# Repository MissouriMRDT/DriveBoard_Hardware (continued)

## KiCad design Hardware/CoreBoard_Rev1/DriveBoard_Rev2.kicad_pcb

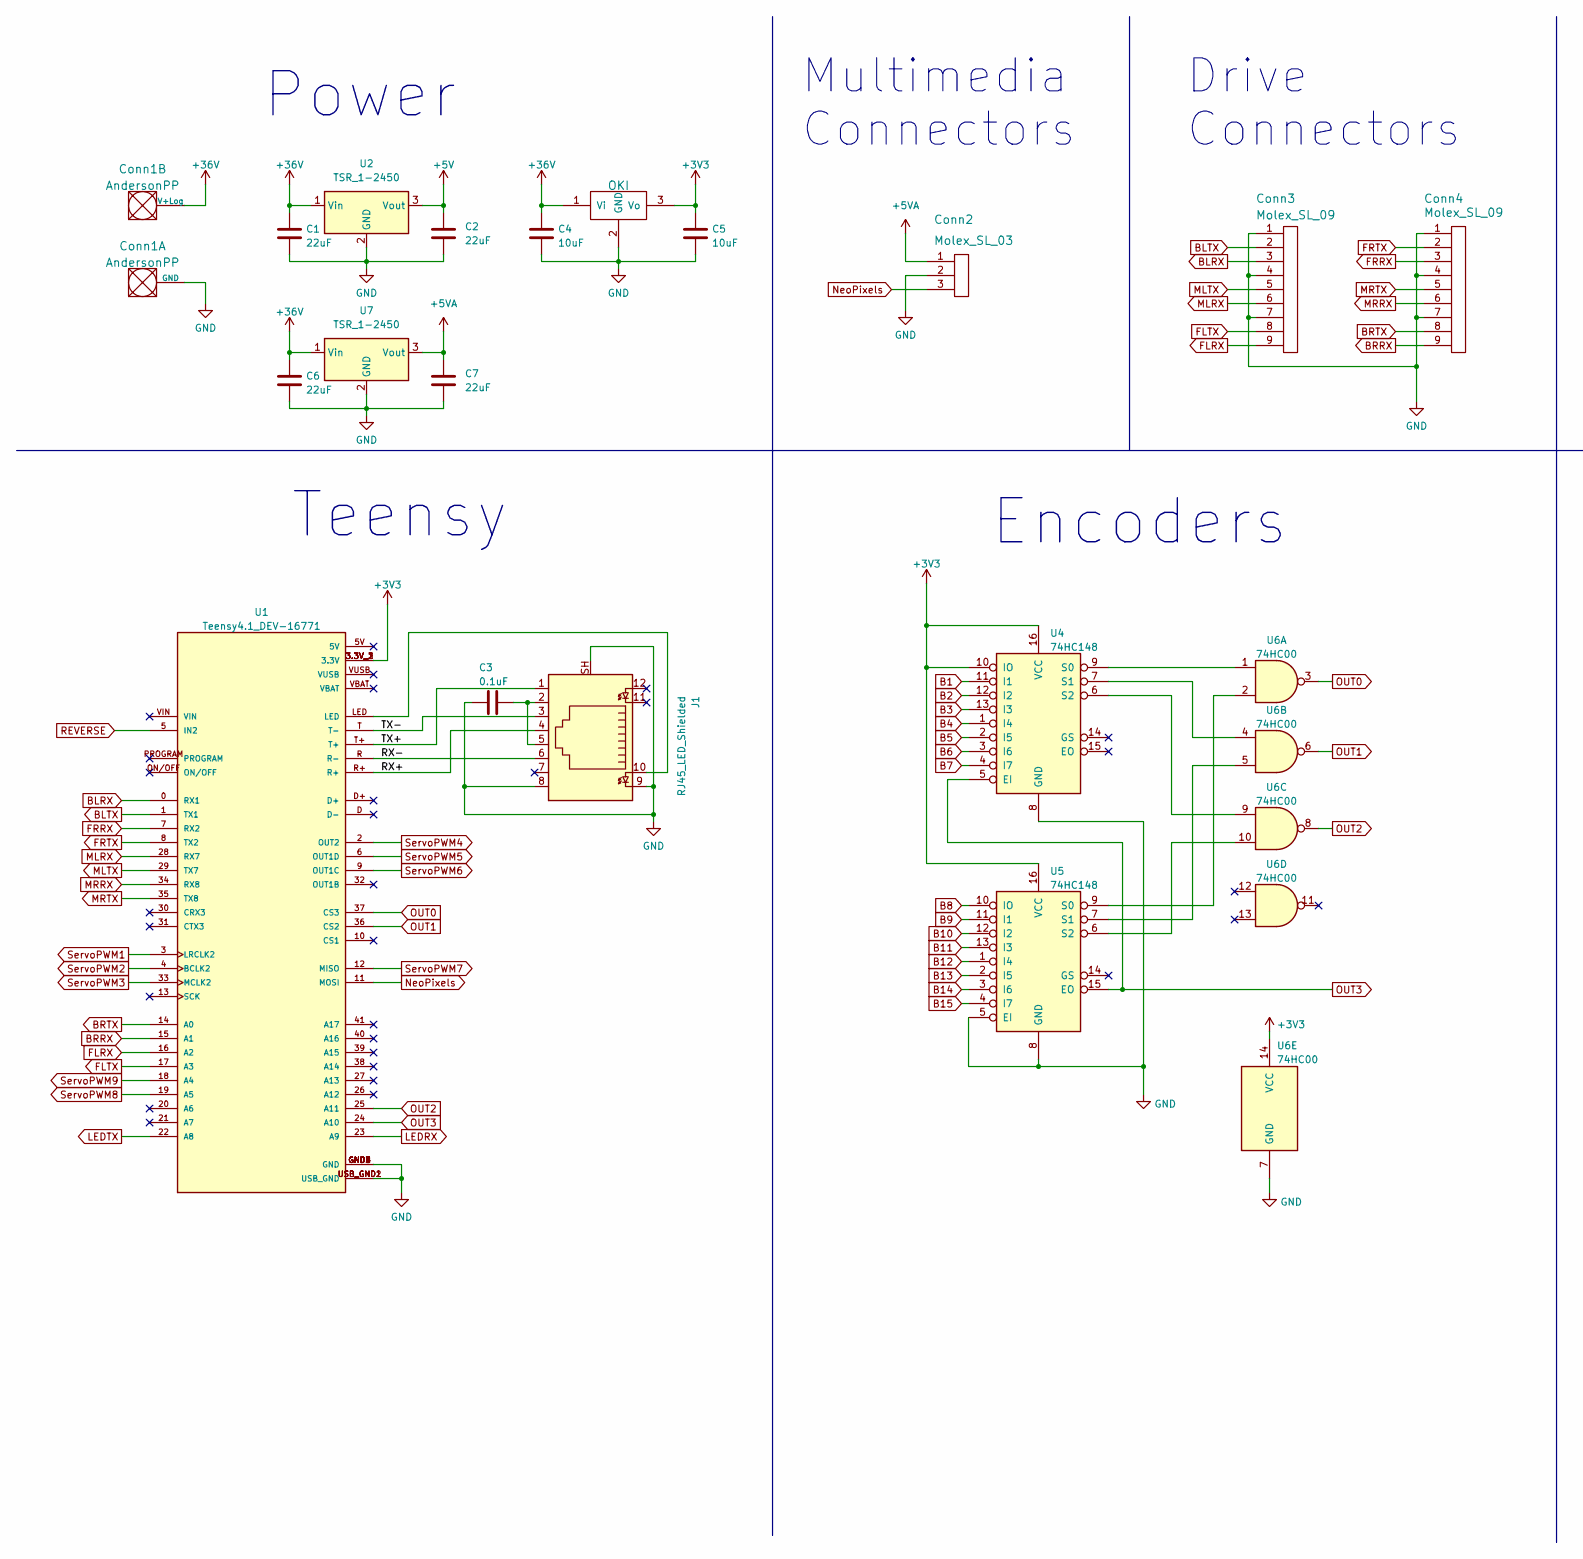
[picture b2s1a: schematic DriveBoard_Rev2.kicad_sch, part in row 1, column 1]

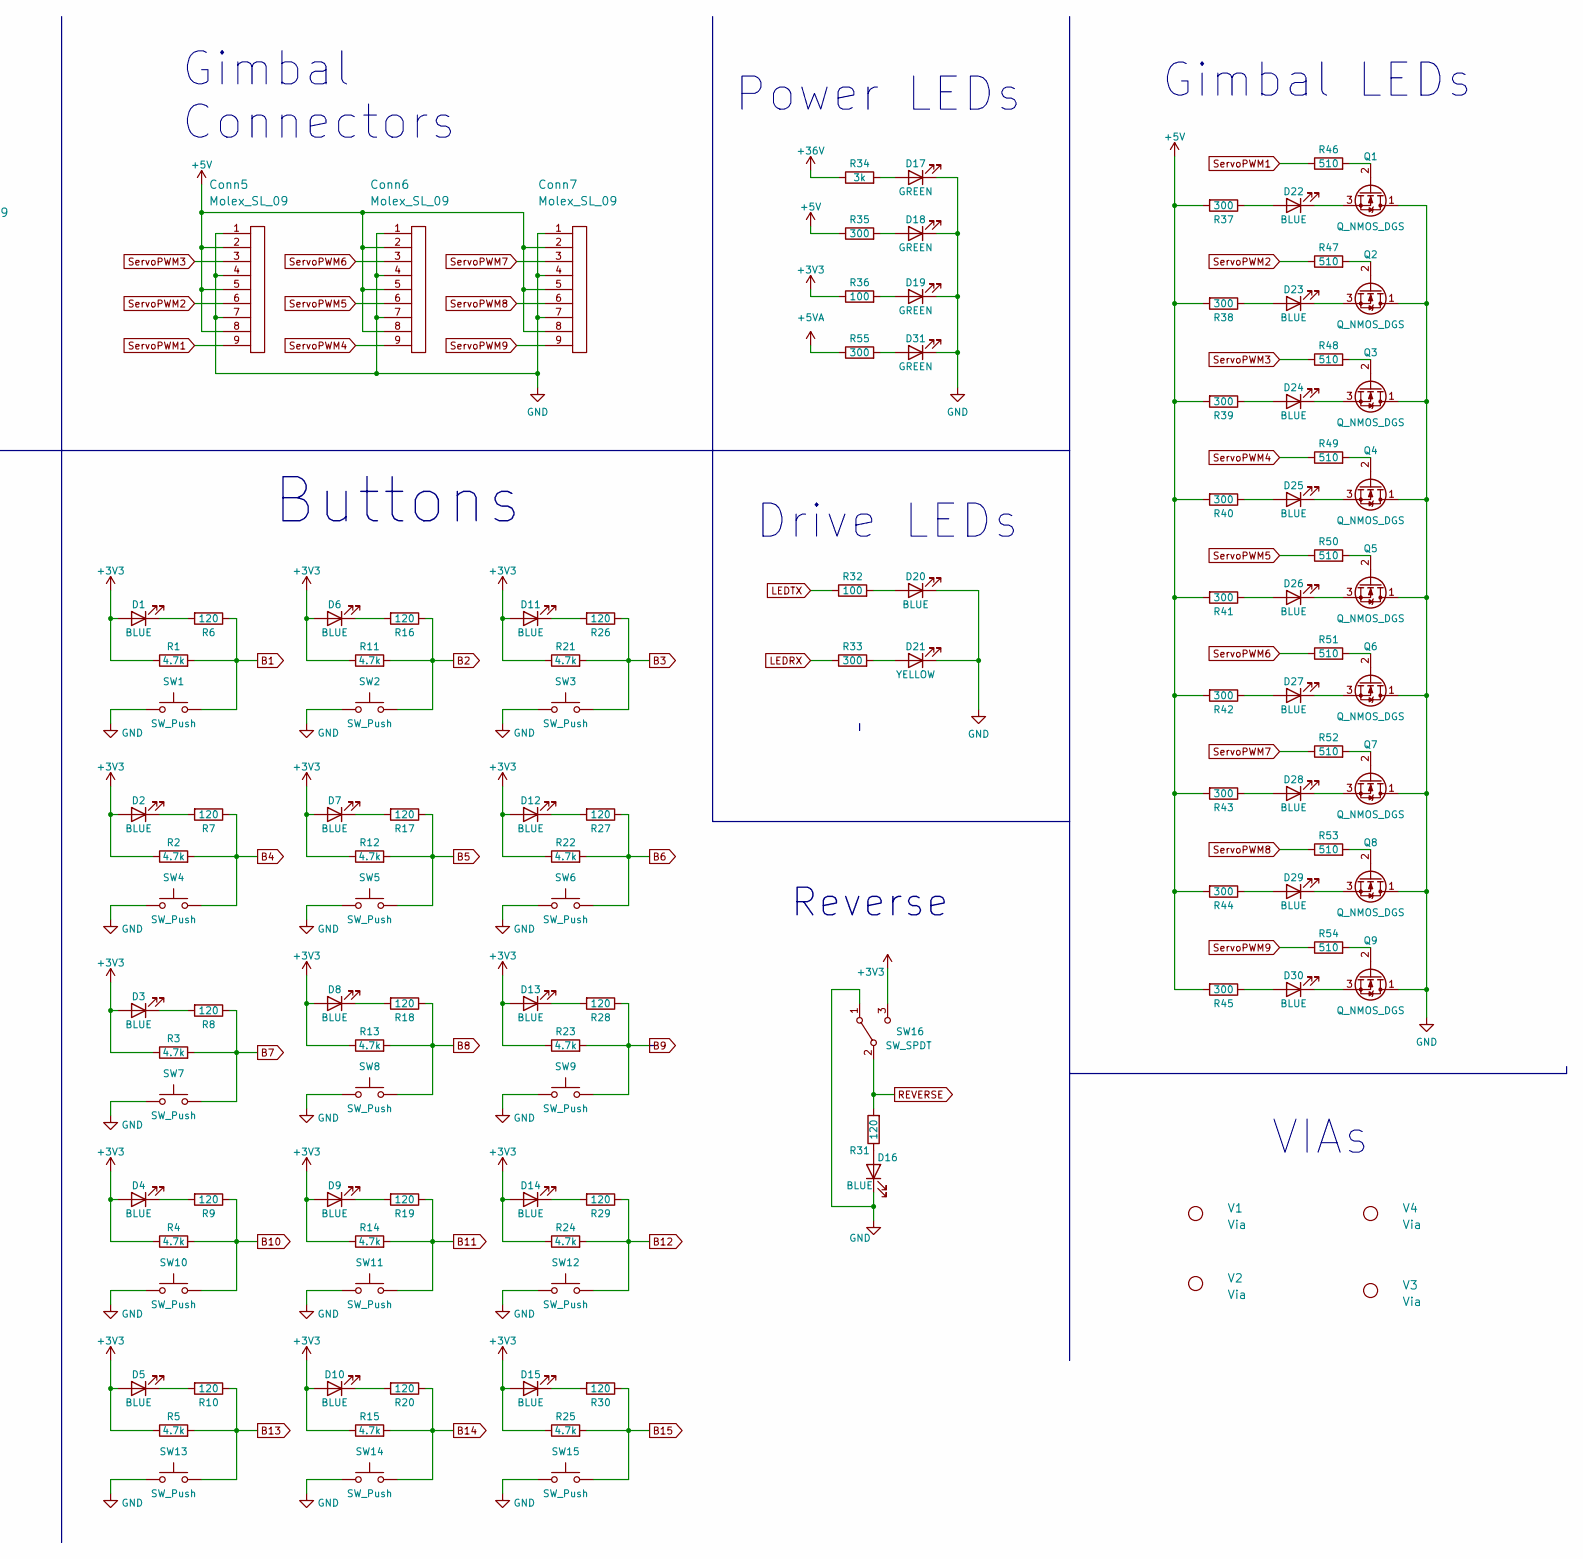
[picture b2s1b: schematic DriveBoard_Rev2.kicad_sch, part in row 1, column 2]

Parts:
C1, C6: 22uF; CP_Radial_D5.0mm_P2.00mm
C2, C7: 22uF; C_0603_1608Metric_Pad1.08x0.95mm_HandSolder
C3: 0.1uF; C_0603_1608Metric_Pad1.08x0.95mm_HandSolder
C4: 10uF; C_1210_3225Metric_Pad1.33x2.70mm_HandSolder
C5: 10uF; C_0603_1608Metric_Pad1.08x0.95mm_HandSolder
Conn1: AndersonPP; Square_Anderson_2_H_Side_By_Side
Conn2: Molex_SL_03; MOLEX_SL_03_Vertical
Conn3, Conn4, Conn5, Conn6, Conn7: Molex_SL_09; MOLEX_SL_09_Vertical
D1, D2, D3, D4, D5, D6, D7, D8, D9, D10, D11, D12, D13, D14, D15, D16, D20, D22, D23, D24, D25, D26, D27, D28, D29, D30: BLUE; LED_0603_1608Metric_Pad1.05x0.95mm_HandSolder
D17, D18, D19, D31: GREEN; LED_0603_1608Metric_Pad1.05x0.95mm_HandSolder
D21: YELLOW; LED_0603_1608Metric_Pad1.05x0.95mm_HandSolder
J1: RJ45_LED_Shielded; RJ45_Teensy
Q1, Q2, Q3, Q4, Q5, Q6, Q7, Q8, Q9: Q_NMOS_DGS; SOT-23
R1, R2, R3, R4, R5, R11, R12, R13, R14, R15, R21, R22, R23, R24, R25: 4.7k; R_0603_1608Metric_Pad0.98x0.95mm_HandSolder
R6, R7, R8, R9, R10, R16, R17, R18, R19, R20, R26, R27, R28, R29, R30, R31: 120; R_0603_1608Metric_Pad0.98x0.95mm_HandSolder
R32, R36: 100; R_0603_1608Metric_Pad0.98x0.95mm_HandSolder
R33, R35, R37, R38, R39, R40, R41, R42, R43, R44, R45, R55: 300; R_0603_1608Metric_Pad0.98x0.95mm_HandSolder
R34: 3k; R_0603_1608Metric_Pad0.98x0.95mm_HandSolder
R46, R47, R48, R49, R50, R51, R52, R53, R54: 510; R_0603_1608Metric_Pad0.98x0.95mm_HandSolder
SW1, SW2, SW3, SW4, SW5, SW6, SW7, SW8, SW9, SW10, SW11, SW12, SW13, SW14, SW15: SW_Push; SW_SPST_TL3305A
SW16: SW_SPDT; SW_Slide_1P2T_CK_OS102011MS2Q
U1: Teensy4.1_DEV-16771; Teensy_4_1_Ethernet; PARTREV 4.1
U2, U7: TSR_1-2450; TSR_1-2433
U3: OKI; OKI_Horizontal
U4, U5: 74HC148; SOIC-16_4.55x10.3mm_P1.27mm
U6: 74HC00; SO-14_5.3x10.2mm_P1.27mm
V1, V2, V3, V4: Via; 4_40_Hole_Corner

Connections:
+3V3: C5.1, D1.2 (A), D2.2 (A), D3.2 (A), D4.2 (A), D5.2 (A), D6.2 (A), D7.2 (A), D8.2 (A), D9.2 (A), D10.2 (A), D11.2 (A), D12.2 (A), D13.2 (A), D14.2 (A), D15.2 (A), R1.1, R2.1, R3.1, R4.1, R5.1, R11.1, R12.1, R13.1, R14.1, R15.1, R21.1, R22.1, R23.1, R24.1, R25.1, R36.1, SW16.3 (C), U1.3.3V_1 (3.3V), U1.3.3V_2 (3.3V), U1.3.3V_3 (3.3V), U3.3 (Vo), U4.10 (IO), U4.16 (VCC), U5.16 (VCC), U6.14 (VCC)
+5V: C2.1, Conn5.2, Conn5.5, Conn5.8, Conn6.2, Conn6.5, Conn6.8, Conn7.2, Conn7.5, Conn7.8, R35.1, R37.2, R38.2, R39.2, R40.2, R41.2, R42.2, R43.2, R44.2, R45.2, U2.3 (Vout)
+5VA: C7.2, Conn2.1, R55.1, U7.3 (Vout)
+36V: C1.1, C4.1, C6.1, Conn1.2 (V+Log), R34.1, U2.1 (Vin), U3.1 (Vi), U7.1 (Vin)
/RX+: J1.4, U1.R+
/RX-: J1.6, U1.R (R-)
/TX+: J1.1, U1.T+
/TX-: J1.3, U1.T (T-)
B1: R1.2, R6.1, SW1.2, U4.11 (I1)
B2: R11.2, R16.1, SW2.2, U4.12 (I2)
B3: R21.2, R26.1, SW3.2, U4.13 (I3)
B4: R2.2, R7.1, SW4.2, U4.1 (I4)
B5: R12.2, R17.1, SW5.2, U4.2 (I5)
B6: R22.2, R27.1, SW6.2, U4.3 (I6)
B7: R3.2, R8.1, SW7.2, U4.4 (I7)
B8: R13.2, R18.1, SW8.2, U5.10 (IO)
B9: R23.2, R28.1, SW9.2, U5.11 (I1)
B10: R4.2, R9.1, SW10.2, U5.12 (I2)
B11: R14.2, R19.1, SW11.2, U5.13 (I3)
B12: R24.2, R29.1, SW12.2, U5.1 (I4)
B13: R5.2, R10.1, SW13.2, U5.2 (I5)
B14: R15.2, R20.1, SW14.2, U5.3 (I6)
B15: R25.2, R30.1, SW15.2, U5.4 (I7)
BLRX: Conn3.3, U1.0 (RX1)
BLTX: Conn3.2, U1.1 (TX1)
BRRX: Conn4.9, U1.15 (A1)
BRTX: Conn4.8, U1.14 (A0)
FLRX: Conn3.9, U1.16 (A2)
FLTX: Conn3.8, U1.17 (A3)
FRRX: Conn4.3, U1.7 (RX2)
FRTX: Conn4.2, U1.8 (TX2)
GND: C1.2, C2.2, C3.2, C4.2, C5.2, C6.2, C7.1, Conn1.1 (GND), Conn2.2, Conn3.1, Conn3.4, Conn3.7, Conn4.1, Conn4.4, Conn4.7, Conn5.1, Conn5.4, Conn5.7, Conn6.1, Conn6.4, Conn6.7, Conn7.1, Conn7.4, Conn7.7, D16.1 (K), D17.1 (K), D18.1 (K), D19.1 (K), D20.1 (K), D21.1 (K), D31.1 (K), J1.8, J1.9, J1.SH, Q1.1 (D), Q2.1 (D), Q3.1 (D), Q4.1 (D), Q5.1 (D), Q6.1 (D), Q7.1 (D), Q8.1 (D), Q9.1 (D), SW1.1, SW2.1, SW3.1, SW4.1, SW5.1, SW6.1, SW7.1, SW8.1, SW9.1, SW10.1, SW11.1, SW12.1, SW13.1, SW14.1, SW15.1, SW16.1 (A), U1.GND1 (GND), U1.GND2 (GND), U1.GND3 (GND), U1.GND4 (GND), U1.GND5 (GND), U1.USB_GND1 (USB_GND), U1.USB_GND2 (USB_GND), U2.2 (GND), U3.2 (GND), U4.8 (GND), U5.5 (EI), U5.8 (GND), U6.7 (GND), U7.2 (GND)
LEDRX: R33.1, U1.23 (A9)
LEDTX: R32.1, U1.22 (A8)
MLRX: Conn3.6, U1.28 (RX7)
MLTX: Conn3.5, U1.29 (TX7)
MRRX: Conn4.6, U1.34 (RX8)
MRTX: Conn4.5, U1.35 (TX8)
NeoPixels: Conn2.3, U1.11 (MOSI)
unnamed: C3.1, J1.2, J1.5
unnamed: D1.1 (K), R6.2
unnamed: D2.1 (K), R7.2
unnamed: D3.1 (K), R8.2
unnamed: D4.1 (K), R9.2
unnamed: D5.1 (K), R10.2
unnamed: D6.1 (K), R16.2
unnamed: D7.1 (K), R17.2
unnamed: D8.1 (K), R18.2
unnamed: D9.1 (K), R19.2
unnamed: D10.1 (K), R20.2
unnamed: D11.1 (K), R26.2
unnamed: D12.1 (K), R27.2
unnamed: D13.1 (K), R28.2
unnamed: D14.1 (K), R29.2
unnamed: D15.1 (K), R30.2
unnamed: D16.2 (A), R31.1
unnamed: D17.2 (A), R34.2
unnamed: D18.2 (A), R35.2
unnamed: D19.2 (A), R36.2
unnamed: D20.2 (A), R32.2
unnamed: D21.2 (A), R33.2
unnamed: D22.1 (K), Q1.3 (S)
unnamed: D22.2 (A), R37.1
unnamed: D23.1 (K), Q2.3 (S)
unnamed: D23.2 (A), R38.1
unnamed: D24.1 (K), Q3.3 (S)
unnamed: D24.2 (A), R39.1
unnamed: D25.1 (K), Q4.3 (S)
unnamed: D25.2 (A), R40.1
unnamed: D26.1 (K), Q5.3 (S)
unnamed: D26.2 (A), R41.1
unnamed: D27.1 (K), Q6.3 (S)
unnamed: D27.2 (A), R42.1
unnamed: D28.1 (K), Q7.3 (S)
unnamed: D28.2 (A), R43.1
unnamed: D29.1 (K), Q8.3 (S)
unnamed: D29.2 (A), R44.1
unnamed: D30.1 (K), Q9.3 (S)
unnamed: D30.2 (A), R45.1
unnamed: D31.2 (A), R55.2
unnamed: J1.10, U1.LED
unnamed: Q1.2 (G), R46.2
unnamed: Q2.2 (G), R47.2
unnamed: Q3.2 (G), R48.2
unnamed: Q4.2 (G), R49.2
unnamed: Q5.2 (G), R50.2
unnamed: Q6.2 (G), R51.2
unnamed: Q7.2 (G), R52.2
unnamed: Q8.2 (G), R53.2
unnamed: Q9.2 (G), R54.2
unnamed: U4.6 (S2), U6.9
unnamed: U4.7 (S1), U6.4
unnamed: U4.9 (S0), U6.1
unnamed: U5.6 (S2), U6.10
unnamed: U5.7 (S1), U6.5
unnamed: U5.9 (S0), U6.2
OUT0: U1.37 (CS3), U6.3
OUT1: U1.36 (CS2), U6.6
OUT2: U1.25 (A11), U6.8
OUT3: U1.24 (A10), U4.5 (EI), U5.15 (EO)
REVERSE: R31.2, SW16.2 (B), U1.5 (IN2)
ServoPWM1: Conn5.9, R46.1, U1.3 (LRCLK2)
ServoPWM2: Conn5.6, R47.1, U1.4 (BCLK2)
ServoPWM3: Conn5.3, R48.1, U1.33 (MCLK2)
ServoPWM4: Conn6.9, R49.1, U1.2 (OUT2)
ServoPWM5: Conn6.6, R50.1, U1.6 (OUT1D)
ServoPWM6: Conn6.3, R51.1, U1.9 (OUT1C)
ServoPWM7: Conn7.3, R52.1, U1.12 (MISO)
ServoPWM8: Conn7.6, R53.1, U1.19 (A5)
ServoPWM9: Conn7.9, R54.1, U1.18 (A4)

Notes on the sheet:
Power LEDs
Power
Drive LEDs
Encoders
Multimedia Connectors
Teensy
Reverse
Gimbal Connectors
Gimbal LEDs
Drive Connectors
Buttons
VIAs

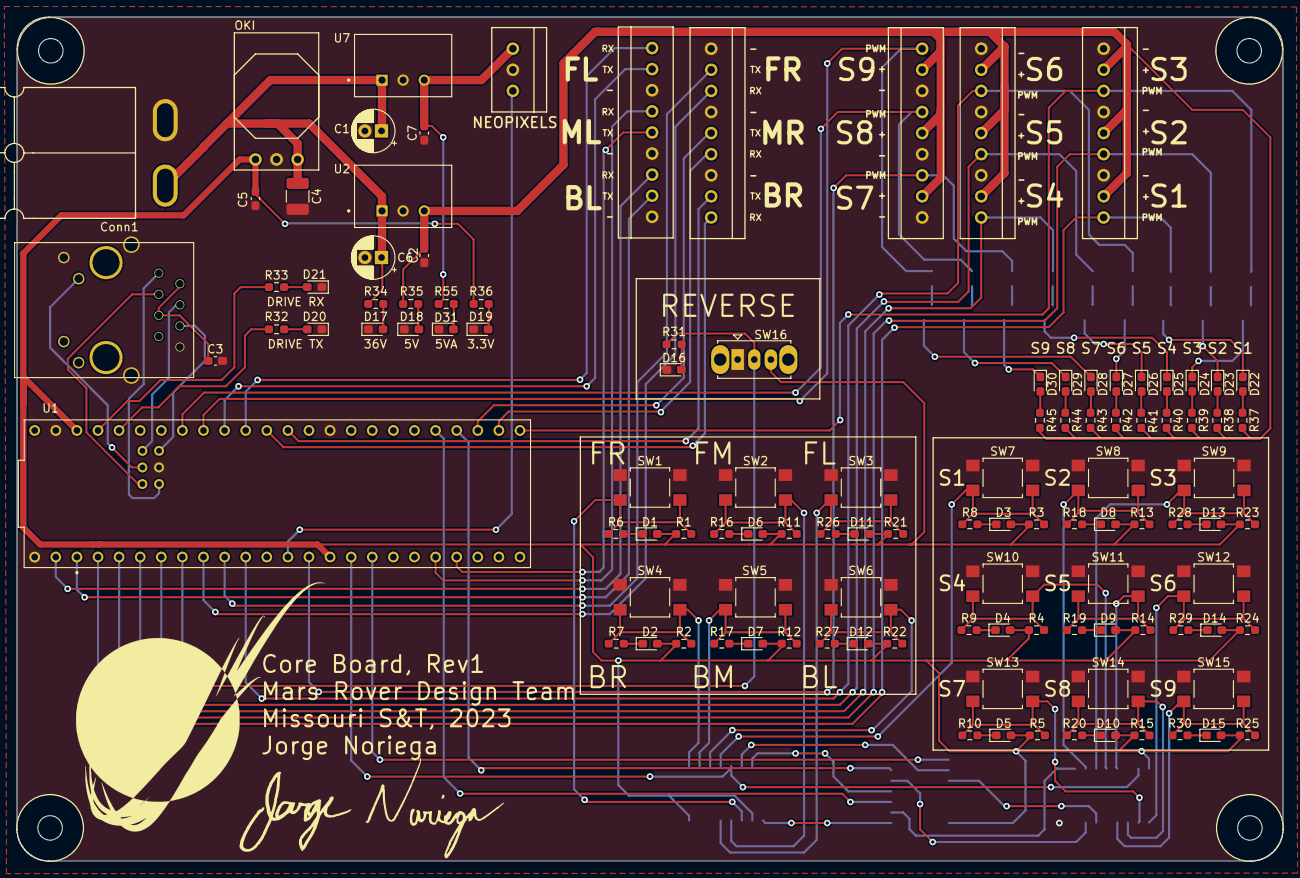
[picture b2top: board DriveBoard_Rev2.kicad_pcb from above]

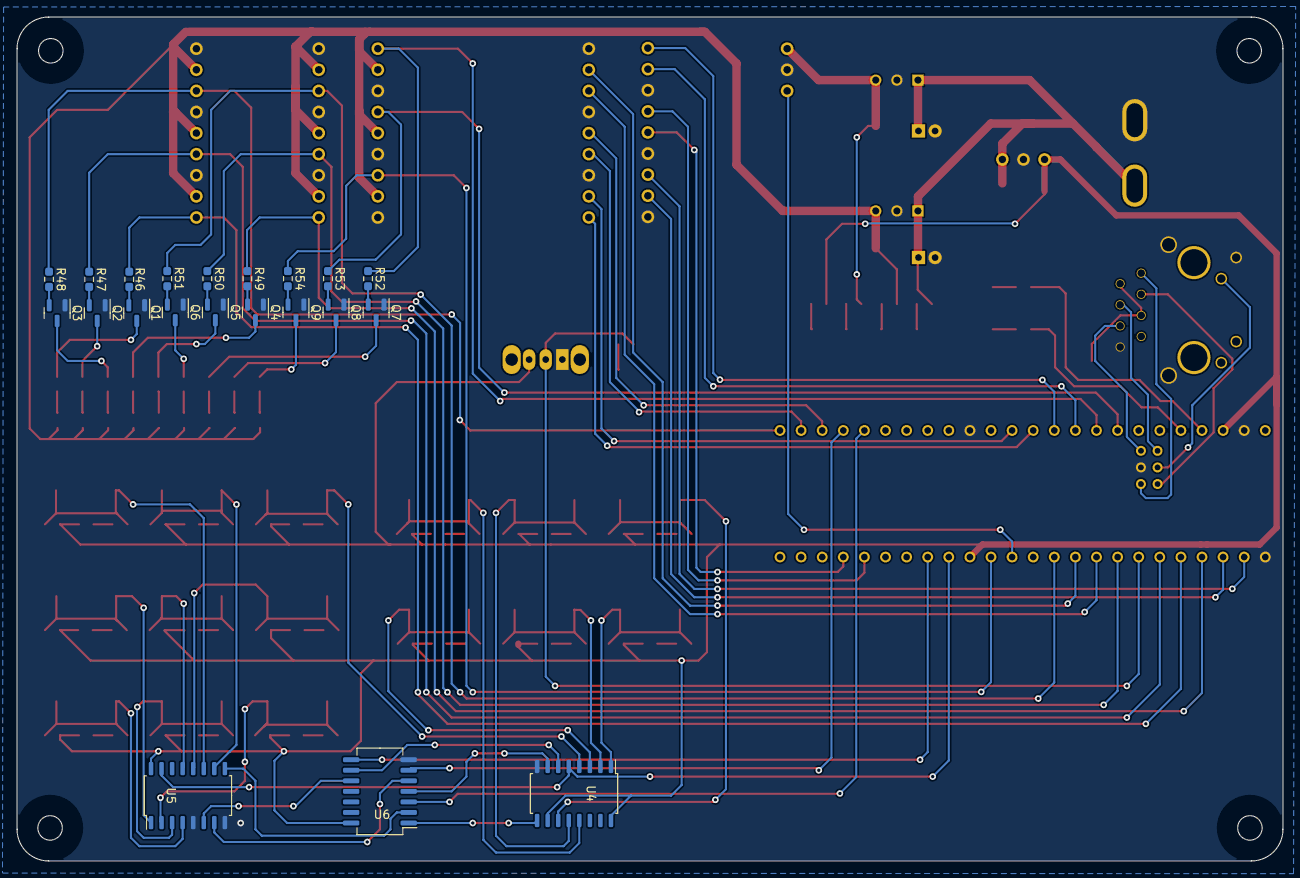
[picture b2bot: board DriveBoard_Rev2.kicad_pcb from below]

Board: 2 copper layers, 152.4 x 101.6 mm, 137 parts (21 on the bottom side), 108 nets.

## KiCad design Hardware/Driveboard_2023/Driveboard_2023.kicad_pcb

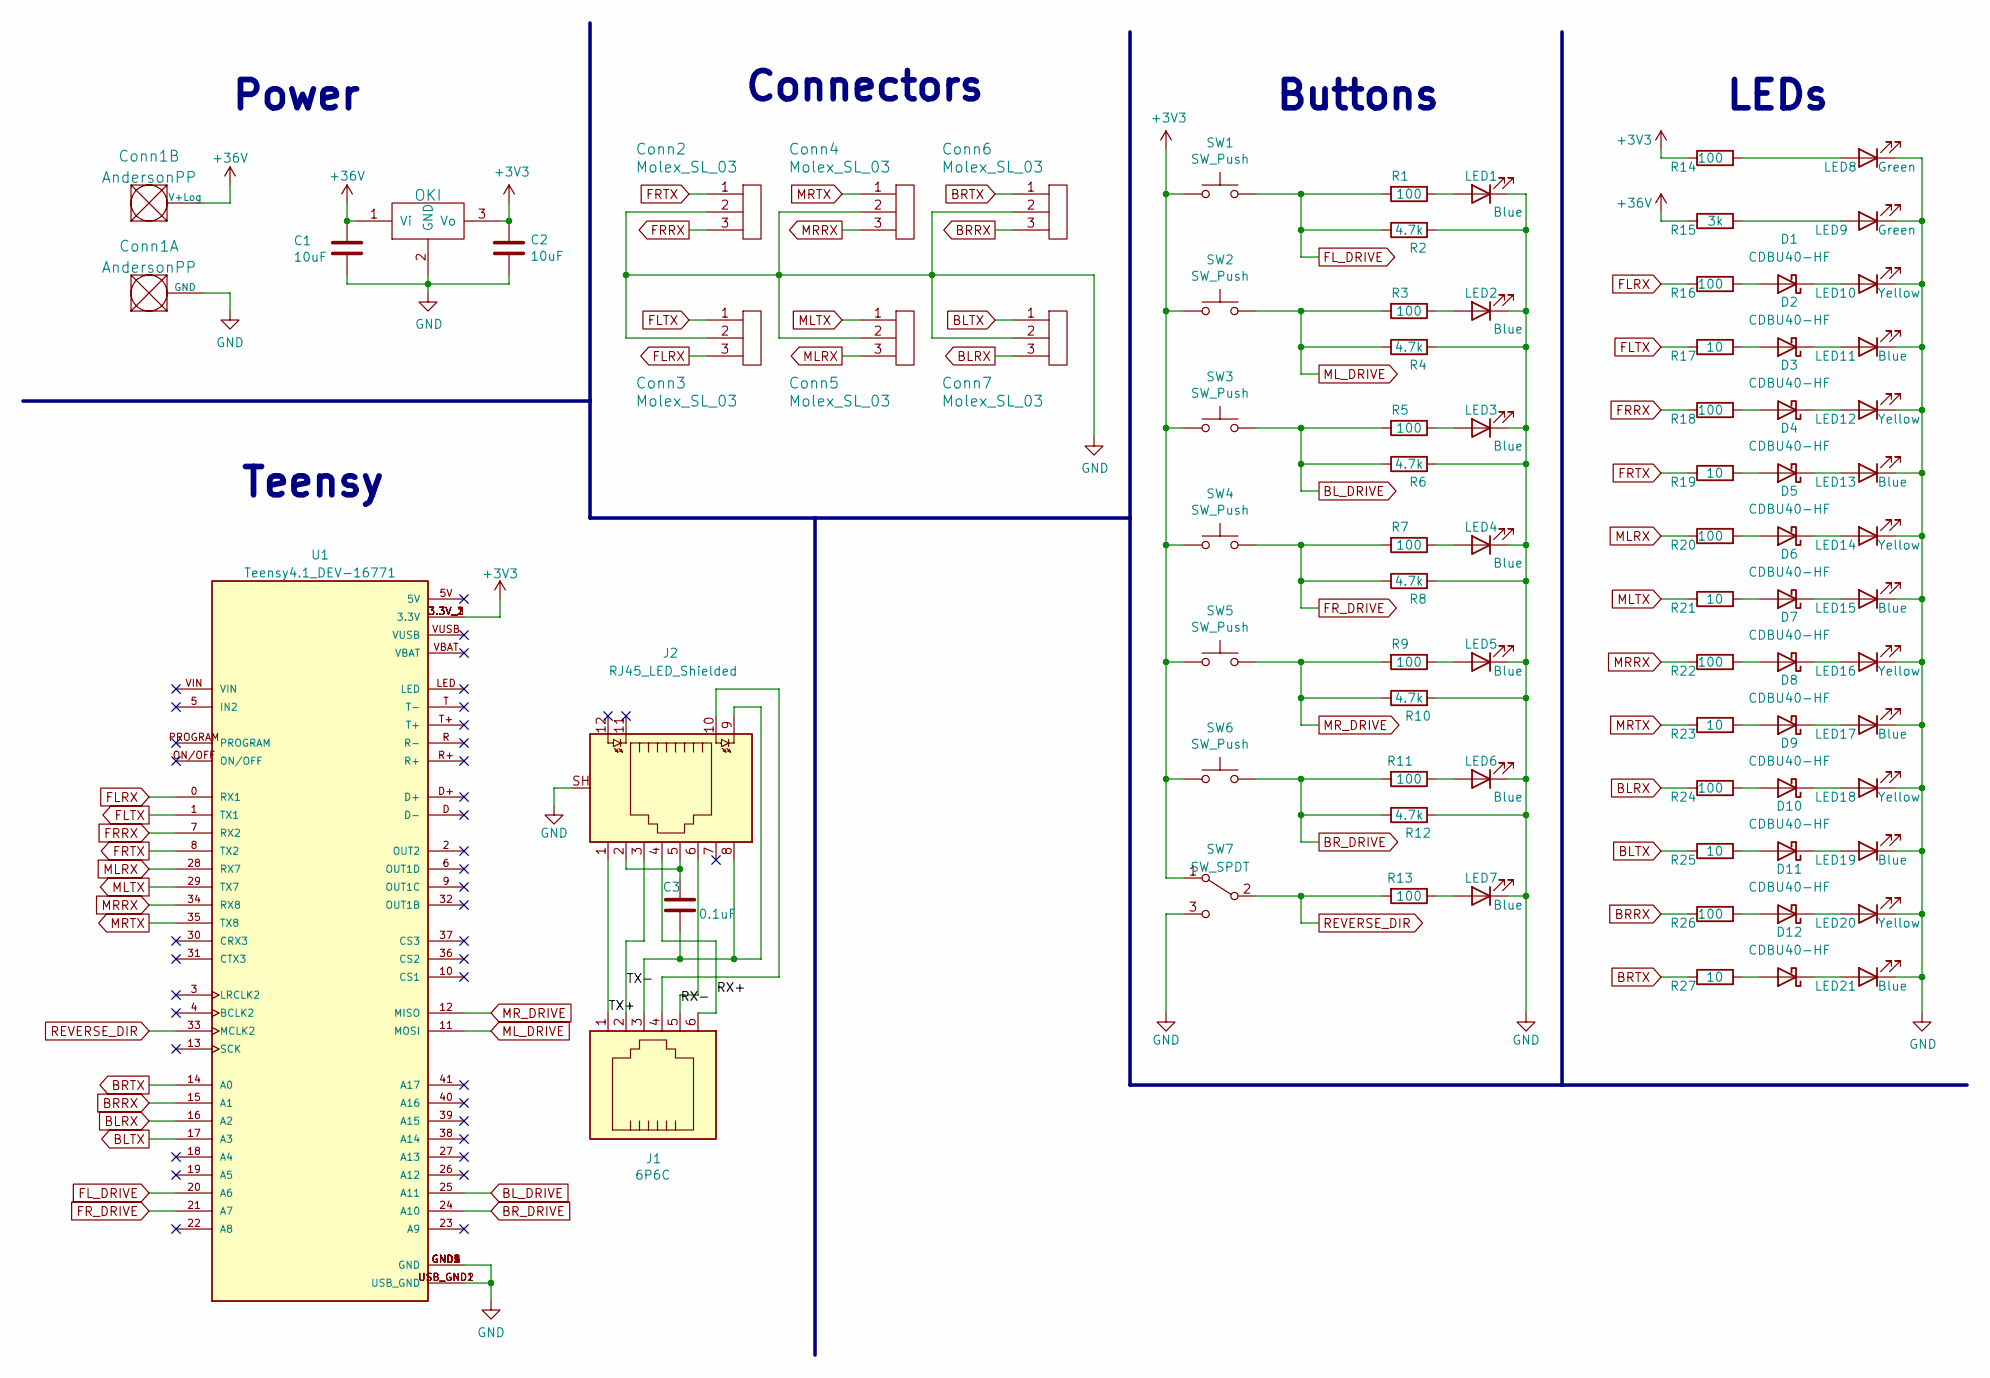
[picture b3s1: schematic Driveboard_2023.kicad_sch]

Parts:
C1, C2: 10uF; C_0603_1608Metric_Pad1.08x0.95mm_HandSolder
C3: 0.1uF; C_0603_1608Metric_Pad1.08x0.95mm_HandSolder
Conn1: AndersonPP; Square_Anderson_2_H_Side_By_Side
Conn2, Conn3, Conn4, Conn5, Conn6, Conn7: Molex_SL_03; MOLEX_SL_03_Horizontal
D1, D2, D3, D4, D5, D6, D7, D8, D9, D10, D11, D12: CDBU40-HF; D_0603_1608Metric_Pad1.05x0.95mm_HandSolder
J1: 6P6C; PinHeader_2x03_P2.00mm_Vertical
J2: RJ45_LED_Shielded; RJ45_Teensy
LED1, LED2, LED3, LED4, LED5, LED6, LED7, LED11, LED13, LED15, LED17, LED19, LED21: Blue; LED_0603_1608Metric_Pad1.05x0.95mm_HandSolder
LED8, LED9: Green; LED_0603_1608Metric_Pad1.05x0.95mm_HandSolder
LED10, LED12, LED14, LED16, LED18, LED20: Yellow; LED_0603_1608Metric_Pad1.05x0.95mm_HandSolder
R1, R3, R5, R7, R9, R11, R13, R14, R16, R18, R20, R22, R24, R26: 100; R_0603_1608Metric_Pad0.98x0.95mm_HandSolder
R2, R4, R6, R8, R10, R12: 4.7k; R_0603_1608Metric_Pad0.98x0.95mm_HandSolder
R15: 3k; R_0603_1608Metric_Pad0.98x0.95mm_HandSolder
R17, R19, R21, R23, R25, R27: 10; R_0603_1608Metric_Pad0.98x0.95mm_HandSolder
SW1, SW2, SW3, SW4, SW5, SW6: SW_Push; SW_SPST_TL3305A
SW7: SW_SPDT; SW_Slide_1P2T_CK_OS102011MS2Q
U1: Teensy4.1_DEV-16771; Teensy_4_1; PARTREV 4.1
U2: OKI; OKI_Horizontal

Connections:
+3V3: C2.1, R14.1, SW1.1, SW2.1, SW3.1, SW4.1, SW5.1, SW6.1, SW7.1 (A), U1.3.3V_1 (3.3V), U1.3.3V_2 (3.3V), U1.3.3V_3 (3.3V), U2.3 (Vo)
+36V: C1.1, Conn1.2 (V+Log), R15.1, U2.1 (Vi)
/RX+: J1.6, J2.4
/RX-: J1.5, J2.6
/TX+: J1.1, J2.1
/TX-: J1.2, J2.3
BLRX: Conn7.3, R24.1, U1.16 (A2)
BLTX: Conn7.1, R25.1, U1.17 (A3)
BL_DRIVE: R5.2, R6.1, SW3.2, U1.25 (A11)
BRRX: Conn6.3, R26.1, U1.15 (A1)
BRTX: Conn6.1, R27.1, U1.14 (A0)
BR_DRIVE: R11.2, R12.1, SW6.2, U1.24 (A10)
FLRX: Conn3.3, R16.1, U1.0 (RX1)
FLTX: Conn3.1, R17.1, U1.1 (TX1)
FL_DRIVE: R1.2, R2.1, SW1.2, U1.20 (A6)
FRRX: Conn2.3, R18.1, U1.7 (RX2)
FRTX: Conn2.1, R19.1, U1.8 (TX2)
FR_DRIVE: R7.2, R8.1, SW4.2, U1.21 (A7)
GND: C1.2, C2.2, Conn1.1 (GND), Conn2.2, Conn3.2, Conn4.2, Conn5.2, Conn6.2, Conn7.2, J2.SH, LED1.1 (K), LED2.1 (K), LED3.1 (K), LED4.1 (K), LED5.1 (K), LED6.1 (K), LED7.1 (K), LED8.1 (K), LED9.1 (K), LED10.1 (K), LED11.1 (K), LED12.1 (K), LED13.1 (K), LED14.1 (K), LED15.1 (K), LED16.1 (K), LED17.1 (K), LED18.1 (K), LED19.1 (K), LED20.1 (K), LED21.1 (K), R2.2, R4.2, R6.2, R8.2, R10.2, R12.2, SW7.3 (C), U1.GND1 (GND), U1.GND2 (GND), U1.GND3 (GND), U1.GND4 (GND), U1.GND5 (GND), U1.USB_GND1 (USB_GND), U1.USB_GND2 (USB_GND), U2.2 (GND)
MLRX: Conn5.3, R20.1, U1.28 (RX7)
MLTX: Conn5.1, R21.1, U1.29 (TX7)
ML_DRIVE: R3.2, R4.1, SW2.2, U1.11 (MOSI)
MRRX: Conn4.3, R22.1, U1.34 (RX8)
MRTX: Conn4.1, R23.1, U1.35 (TX8)
MR_DRIVE: R9.2, R10.1, SW5.2, U1.12 (MISO)
unnamed: C3.1, J2.2, J2.5
unnamed: C3.2, J1.3, J2.8, J2.9
unnamed: D1.1 (K), LED10.2 (A)
unnamed: D1.2 (A), R16.2
unnamed: D2.1 (K), LED11.2 (A)
unnamed: D2.2 (A), R17.2
unnamed: D3.1 (K), LED12.2 (A)
unnamed: D3.2 (A), R18.2
unnamed: D4.1 (K), LED13.2 (A)
unnamed: D4.2 (A), R19.2
unnamed: D5.1 (K), LED14.2 (A)
unnamed: D5.2 (A), R20.2
unnamed: D6.1 (K), LED15.2 (A)
unnamed: D6.2 (A), R21.2
unnamed: D7.1 (K), LED16.2 (A)
unnamed: D7.2 (A), R22.2
unnamed: D8.1 (K), LED17.2 (A)
unnamed: D8.2 (A), R23.2
unnamed: D9.1 (K), LED18.2 (A)
unnamed: D9.2 (A), R24.2
unnamed: D10.1 (K), LED19.2 (A)
unnamed: D10.2 (A), R25.2
unnamed: D11.1 (K), LED20.2 (A)
unnamed: D11.2 (A), R26.2
unnamed: D12.1 (K), LED21.2 (A)
unnamed: D12.2 (A), R27.2
unnamed: J1.4, J2.10
unnamed: LED1.2 (A), R1.1
unnamed: LED2.2 (A), R3.1
unnamed: LED3.2 (A), R5.1
unnamed: LED4.2 (A), R7.1
unnamed: LED5.2 (A), R9.1
unnamed: LED6.2 (A), R11.1
unnamed: LED7.2 (A), R13.1
unnamed: LED8.2 (A), R14.2
unnamed: LED9.2 (A), R15.2
REVERSE_DIR: R13.2, SW7.2 (B), U1.33 (MCLK2)

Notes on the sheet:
Teensy
Connectors
Buttons
LEDs
Power

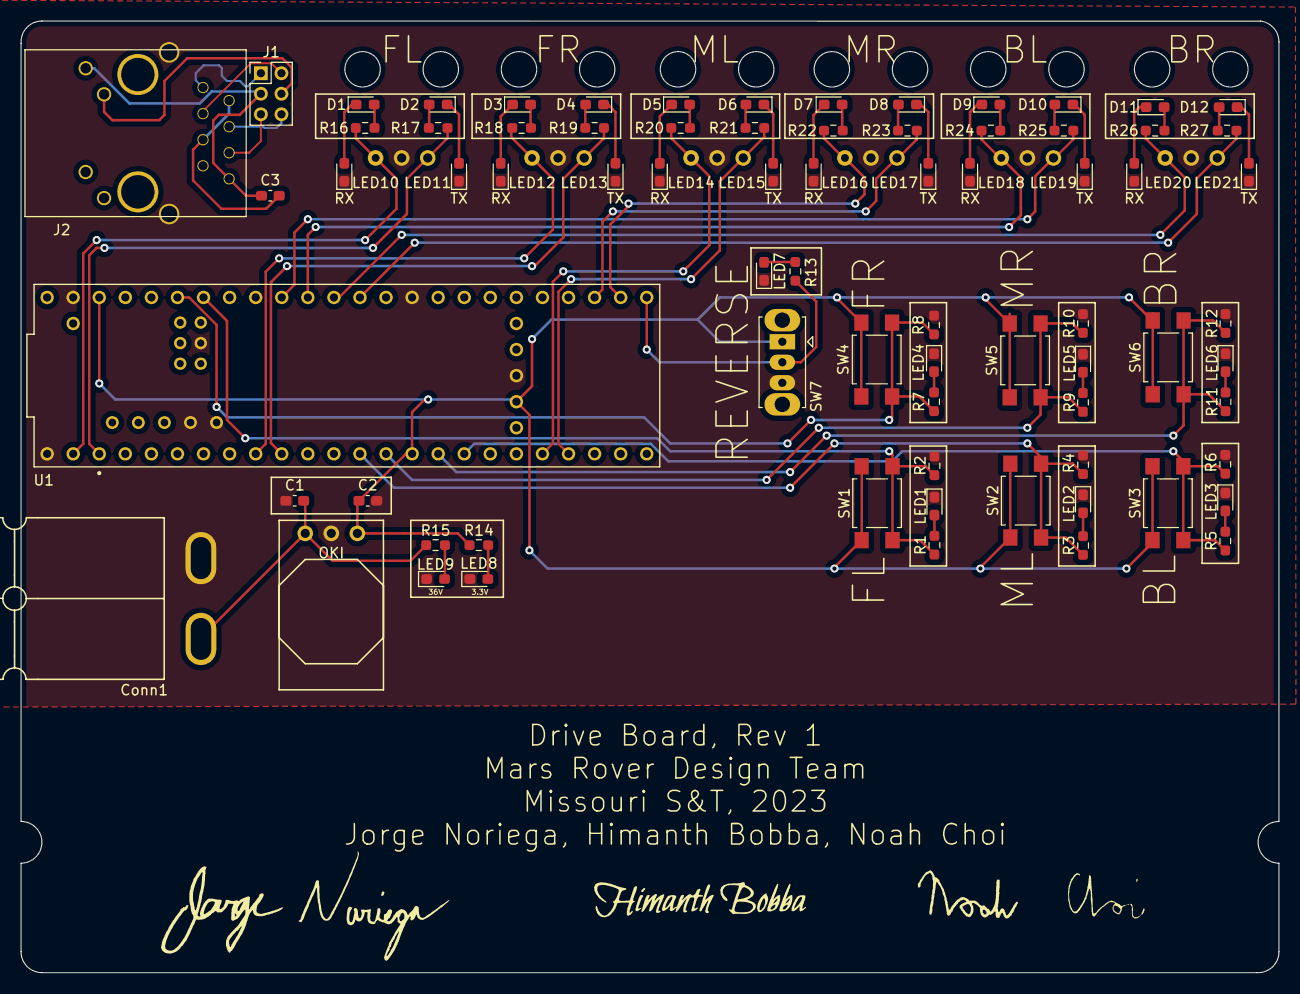
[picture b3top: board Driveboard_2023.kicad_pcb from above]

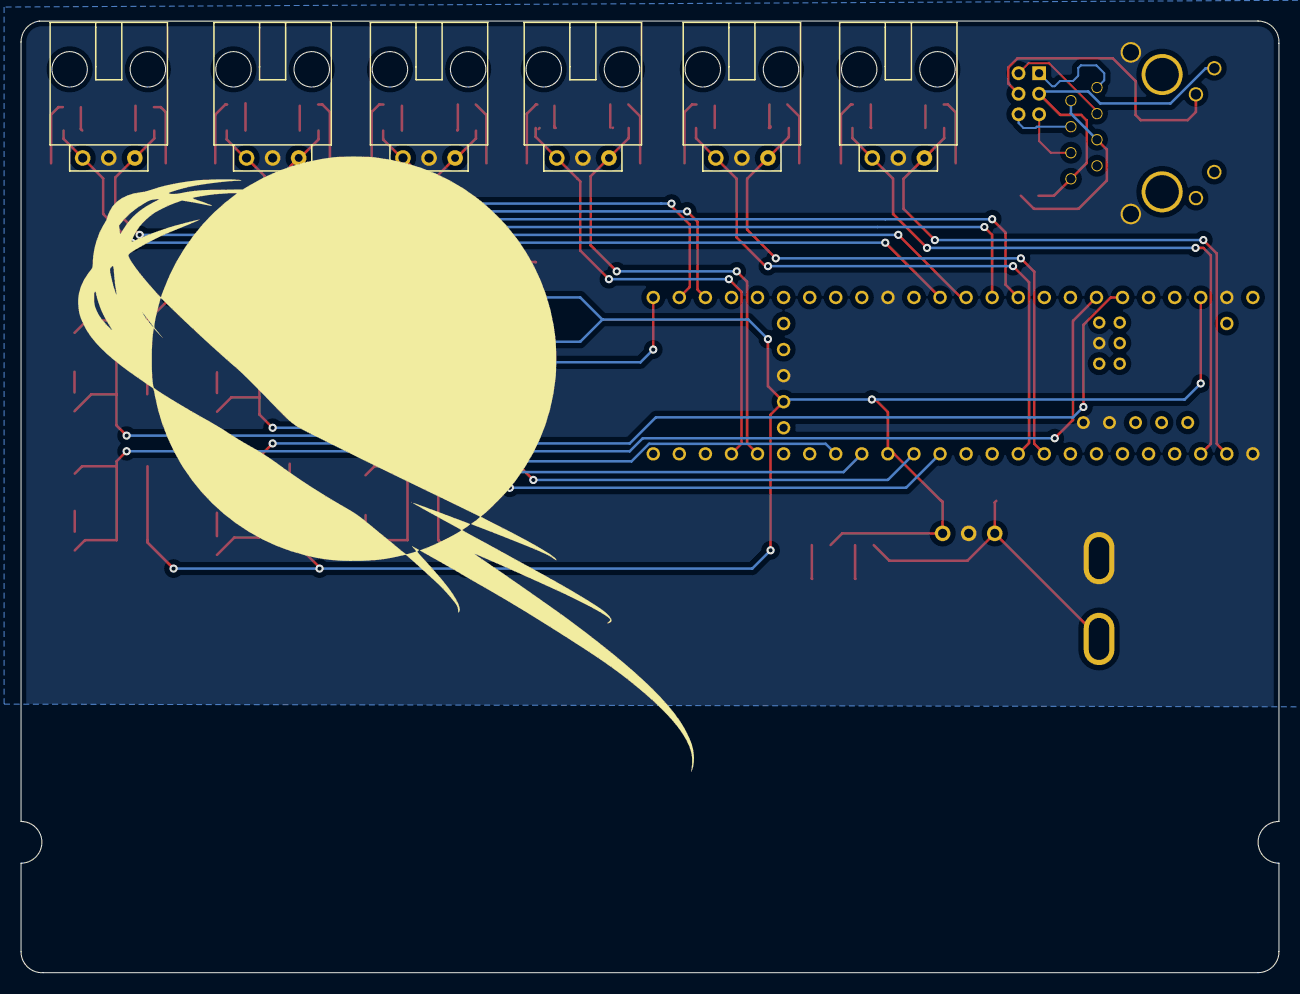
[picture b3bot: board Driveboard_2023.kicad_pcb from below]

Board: 2 copper layers, 122.6 x 92.7 mm, 81 parts (6 on the bottom side), 62 nets.
